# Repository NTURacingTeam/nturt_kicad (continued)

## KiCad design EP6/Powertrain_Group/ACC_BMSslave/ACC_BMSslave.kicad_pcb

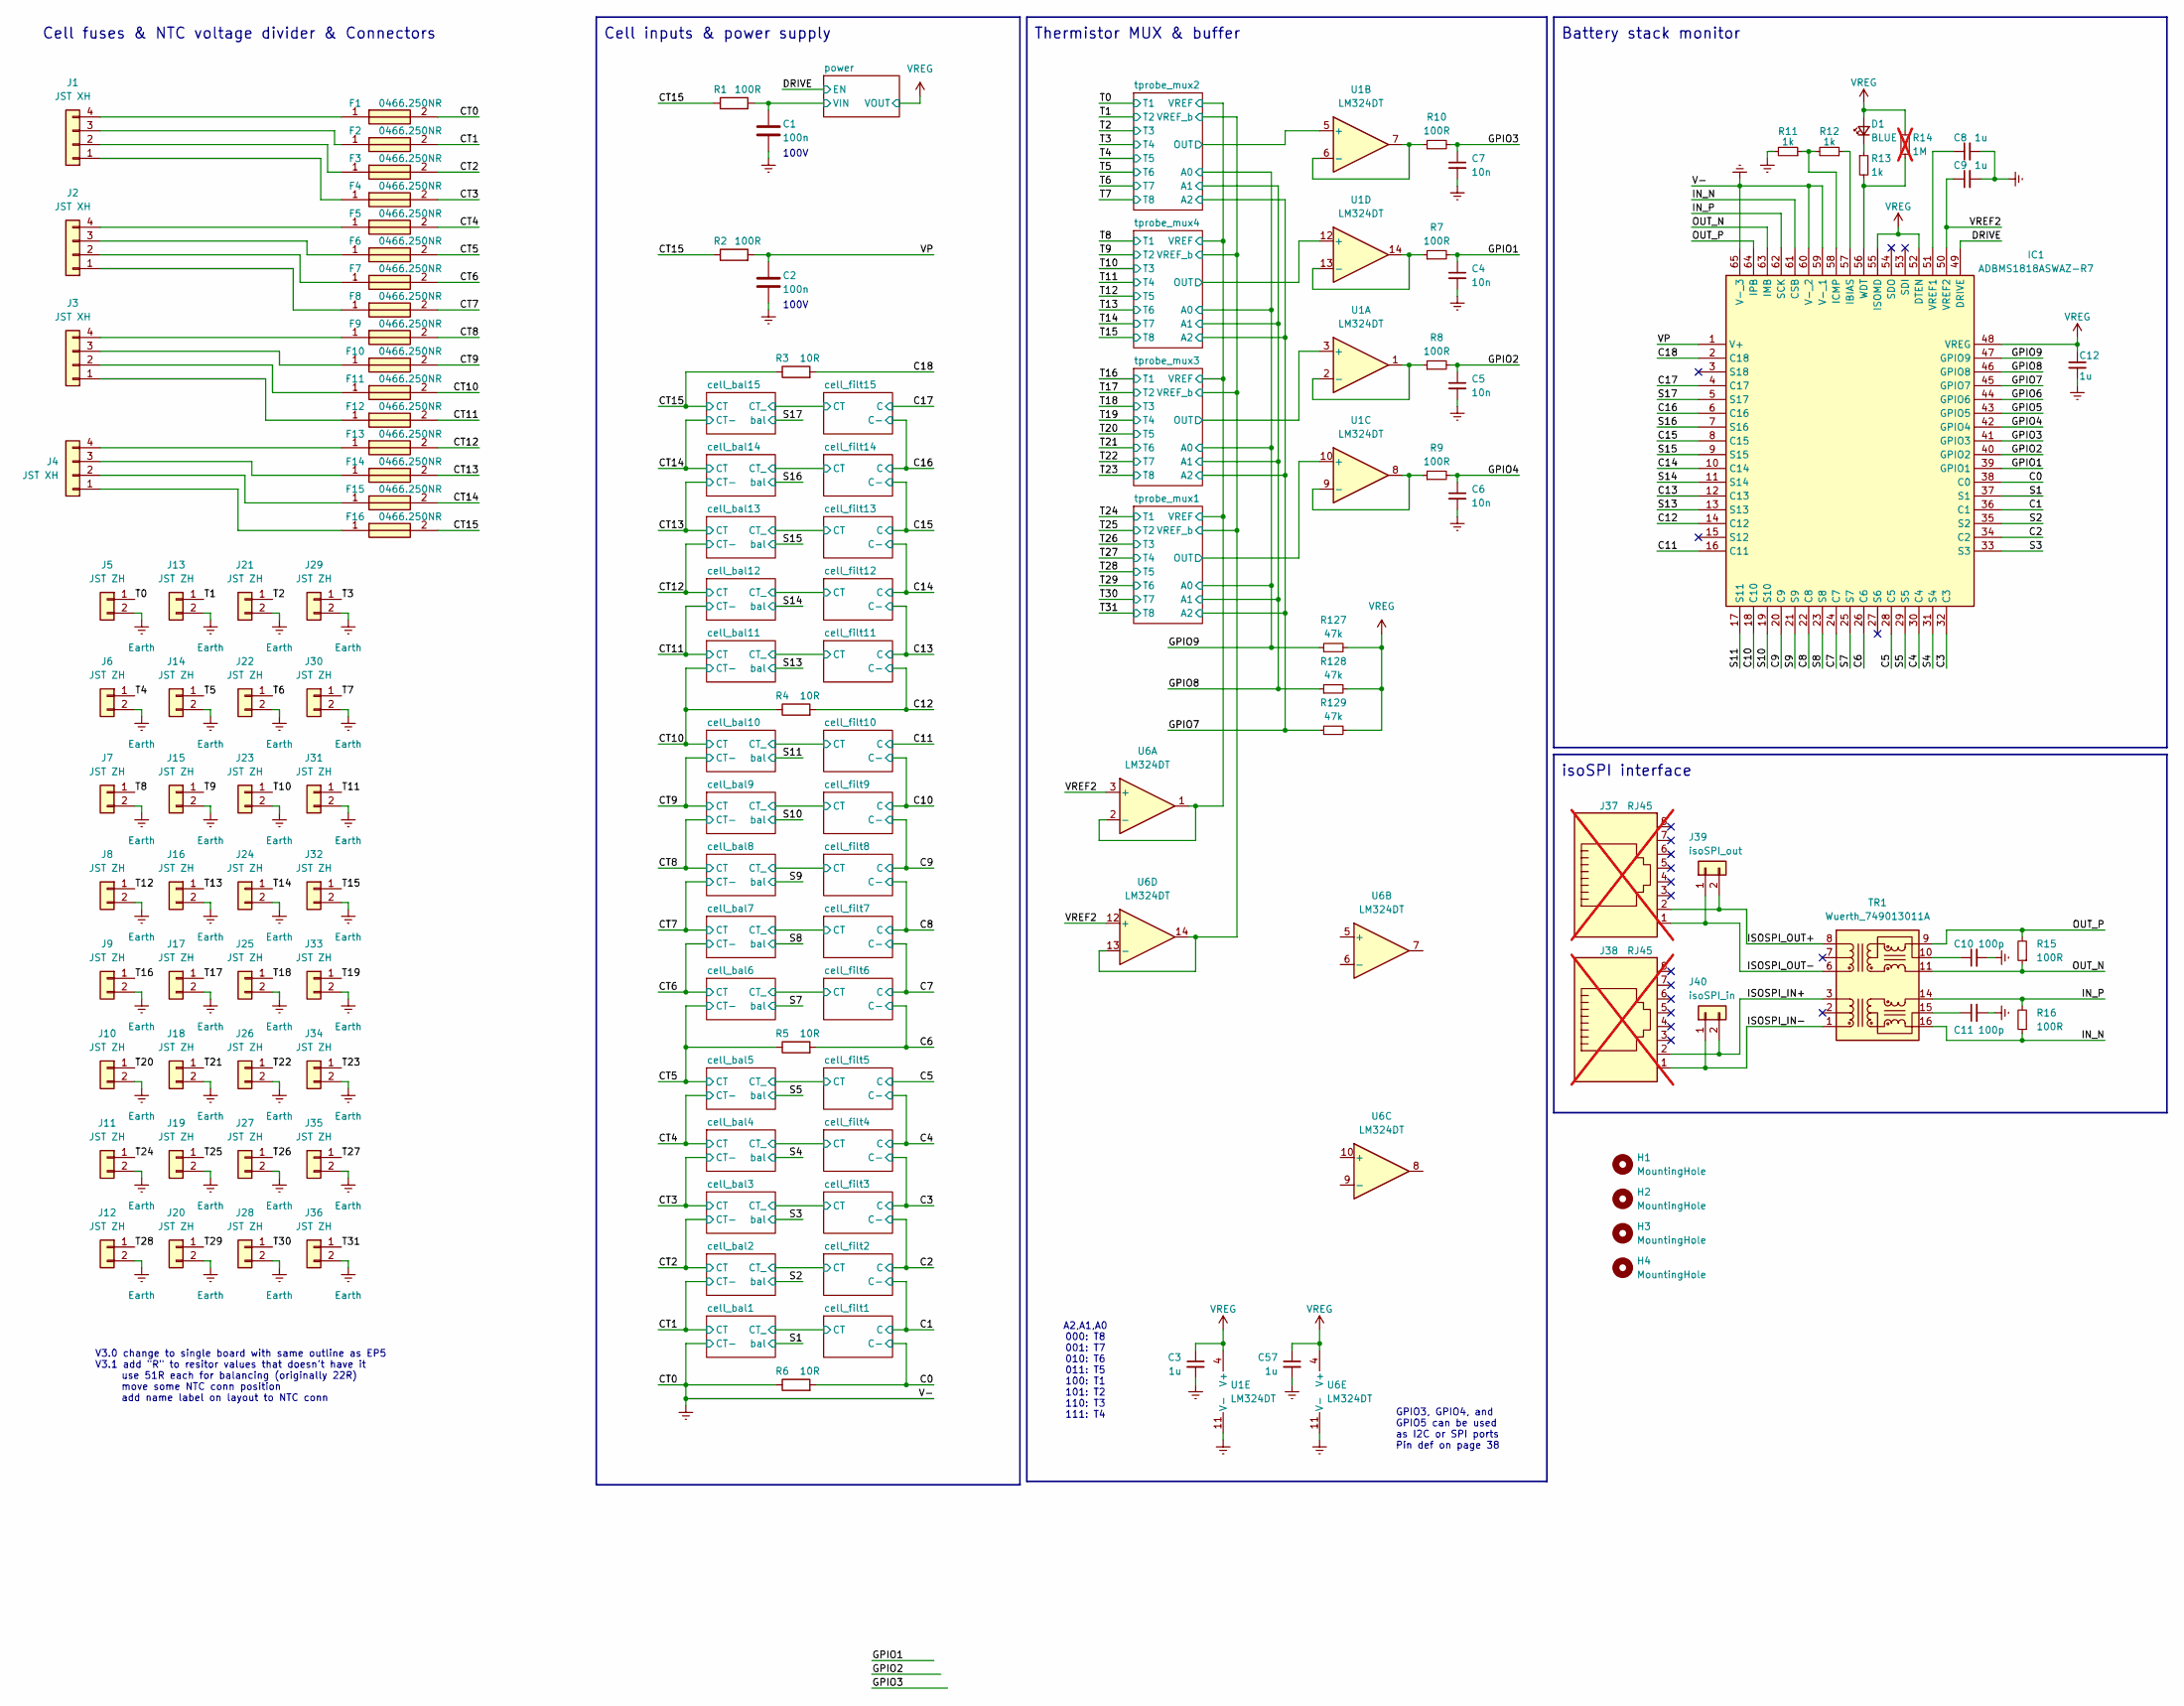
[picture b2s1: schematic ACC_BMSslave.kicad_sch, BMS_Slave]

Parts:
C1, C2: 100n; C_0603_1608Metric
C3, C57: 1u; C_0603_1608Metric
C4, C5, C6, C7: 10n; C_0402_1005Metric
C8, C9: 1u; C_0402_1005Metric
C10, C11: 100p; C_0402_1005Metric
C12: 1u; C_0805_2012Metric
D1: BLUE; LED_0603_1608Metric
F1, F2, F3, F4, F5, F6, F7, F8, F9, F10, F11, F12, F13, F14, F15, F16: 0466.250NR; Fuse_1206_3216Metric; Mouser Part Number 576-0466.250NR
H1, H2, H3, H4: MountingHole; MountingHole_4.3mm_M4_ISO14580
IC1: ADBMS1818ASWAZ-R7; LQFP-64-1EP_10x10mm_P0.5mm_EP6.5x6.5mm; Mouser Part Number 584-ADBMS1818ASWAZR7
J1, J2, J3, J4: JST XH; JST_XH_B4B-XH-A_1x04_P2.50mm_Vertical
J5, J6, J7, J8, J9, J10, J11, J12, J13, J14, J15, J16, J17, J18, J19, J20, J21, J22, J23, J24, J25, J26, J27, J28, J29, J30, J31, J32, J33, J34, J35, J36: JST ZH; JST_ZH_B2B-ZR_1x02_P1.50mm_Vertical
J37, J38: RJ45; RJ45_Amphenol_54602-x08_Horizontal; not fitted
J39: isoSPI_out; JST_XH_B2B-XH-A_1x02_P2.50mm_Vertical
J40: isoSPI_in; JST_XH_B2B-XH-A_1x02_P2.50mm_Vertical
R1: 100R; R_0805_2012Metric
R2: 100R; R_0603_1608Metric
R3, R4, R5, R6: 10R; R_0402_1005Metric
R7, R8, R9, R10, R15, R16: 100R; R_0402_1005Metric
R11, R12, R13: 1k; R_0402_1005Metric
R14: 1M; R_0603_1608Metric; not fitted
R127, R128, R129: 47k; R_0402_1005Metric
TR1: Wuerth_749013011A; Transformer_Ethernet_Wuerth_749013011A
U1, U6: LM324DT; SO-14_3.9x8.65mm_P1.27mm

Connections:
/C0: IC1.38 (C0), R6.2; also elsewhere on the board
/C1: IC1.36 (C1); also elsewhere on the board
/C2: IC1.34 (C2); also elsewhere on the board
/C3: IC1.32 (C3); also elsewhere on the board
/C4: IC1.30 (C4); also elsewhere on the board
/C5: IC1.28 (C5); also elsewhere on the board
/C6: IC1.26 (C6), R5.2; also elsewhere on the board
/C7: IC1.24 (C7); also elsewhere on the board
/C8: IC1.22 (C8); also elsewhere on the board
/C9: IC1.20 (C9); also elsewhere on the board
/C10: IC1.18 (C10); also elsewhere on the board
/C11: IC1.16 (C11); also elsewhere on the board
/C12: IC1.14 (C12), R4.2; also elsewhere on the board
/C13: IC1.12 (C13); also elsewhere on the board
/C14: IC1.10 (C14); also elsewhere on the board
/C15: IC1.8 (C15); also elsewhere on the board
/C16: IC1.6 (C16); also elsewhere on the board
/C17: IC1.4 (C17); also elsewhere on the board
/C18: IC1.2 (C18), R3.2
/CT1: F2.2; also elsewhere on the board
/CT2: F3.2; also elsewhere on the board
/CT3: F4.2; also elsewhere on the board
/CT4: F5.2; also elsewhere on the board
/CT5: F6.2, R5.1; also elsewhere on the board
/CT6: F7.2; also elsewhere on the board
/CT7: F8.2; also elsewhere on the board
/CT8: F9.2; also elsewhere on the board
/CT9: F10.2; also elsewhere on the board
/CT10: F11.2, R4.1; also elsewhere on the board
/CT11: F12.2; also elsewhere on the board
/CT12: F13.2; also elsewhere on the board
/CT13: F14.2; also elsewhere on the board
/CT14: F15.2; also elsewhere on the board
/CT15: F16.2, R1.1, R2.1, R3.1; also elsewhere on the board
/DRIVE: IC1.49 (DRIVE); also elsewhere on the board
/GPIO1: C4.1, IC1.39 (GPIO1), R7.2
/GPIO2: C5.1, IC1.40 (GPIO2), R8.2
/GPIO3: C7.1, IC1.41 (GPIO3), R10.2
/GPIO4: C6.1, IC1.42 (GPIO4), R9.2
/GPIO5: IC1.43 (GPIO5)
/GPIO6: IC1.44 (GPIO6)
/GPIO7: IC1.45 (GPIO7), R129.1; also elsewhere on the board
/GPIO8: IC1.46 (GPIO8), R128.1; also elsewhere on the board
/GPIO9: IC1.47 (GPIO9), R127.1; also elsewhere on the board
/IN_N: IC1.61 (CSB), R16.1, TR1.16 (TX+)
/IN_P: IC1.62 (SCK), R16.2, TR1.14 (TX-)
/ISOSPI_IN+: J38.2, J40.2, TR1.3 (TD-)
/ISOSPI_IN-: J38.1, J40.1, TR1.1 (TD+)
/ISOSPI_OUT+: J37.2, J39.2, TR1.8 (RD-)
/ISOSPI_OUT-: J37.1, J39.1, TR1.6 (RD+)
/OUT_N: IC1.63 (IMB), R15.1, TR1.11 (RX+)
/OUT_P: IC1.64 (IPB), R15.2, TR1.9 (RX-)
/S1: IC1.37 (S1); also elsewhere on the board
/S2: IC1.35 (S2); also elsewhere on the board
/S3: IC1.33 (S3); also elsewhere on the board
/S4: IC1.31 (S4); also elsewhere on the board
/S5: IC1.29 (S5); also elsewhere on the board
/S7: IC1.25 (S7); also elsewhere on the board
/S8: IC1.23 (S8); also elsewhere on the board
/S9: IC1.21 (S9); also elsewhere on the board
/S10: IC1.19 (S10); also elsewhere on the board
/S11: IC1.17 (S11); also elsewhere on the board
/S13: IC1.13 (S13); also elsewhere on the board
/S14: IC1.11 (S14); also elsewhere on the board
/S15: IC1.9 (S15); also elsewhere on the board
/S16: IC1.7 (S16); also elsewhere on the board
/S17: IC1.5 (S17); also elsewhere on the board
/T0: J5.1; also elsewhere on the board
/T1: J13.1; also elsewhere on the board
/T2: J21.1; also elsewhere on the board
/T3: J29.1; also elsewhere on the board
/T4: J6.1; also elsewhere on the board
/T5: J14.1; also elsewhere on the board
/T6: J22.1; also elsewhere on the board
/T7: J30.1; also elsewhere on the board
/T8: J7.1; also elsewhere on the board
/T9: J15.1; also elsewhere on the board
/T10: J23.1; also elsewhere on the board
/T11: J31.1; also elsewhere on the board
/T12: J8.1; also elsewhere on the board
/T13: J16.1; also elsewhere on the board
/T14: J24.1; also elsewhere on the board
/T15: J32.1; also elsewhere on the board
/T16: J9.1; also elsewhere on the board
/T17: J17.1; also elsewhere on the board
/T18: J25.1; also elsewhere on the board
/T19: J33.1; also elsewhere on the board
/T20: J10.1; also elsewhere on the board
/T21: J18.1; also elsewhere on the board
/T22: J26.1; also elsewhere on the board
/T23: J34.1; also elsewhere on the board
/T24: J11.1; also elsewhere on the board
/T25: J19.1; also elsewhere on the board
/T26: J27.1; also elsewhere on the board
/T27: J35.1; also elsewhere on the board
/T28: J12.1; also elsewhere on the board
/T29: J20.1; also elsewhere on the board
/T30: J28.1; also elsewhere on the board
/T31: J36.1; also elsewhere on the board
/VP: C2.1, IC1.1 (V+), R2.2
/VREF2: C9.1, IC1.50 (VREF2), U6.3 (+), U6.12 (+)
/power/VIN: C1.1, R1.2; also elsewhere on the board
/tprobe_mux1/OUT: U1.10 (+); also elsewhere on the board
/tprobe_mux2/OUT: U1.5 (+); also elsewhere on the board
/tprobe_mux3/OUT: U1.3 (+); also elsewhere on the board
/tprobe_mux4/OUT: U1.12 (+); also elsewhere on the board
Earth: C1.2, C2.2, C3.2, C4.2, C5.2, C6.2, C7.2, C8.2, C9.2, C10.2, C11.2, C12.2, C57.2, F1.2, IC1.59 (V-_1), IC1.60 (V-_2), IC1.65 (V-_3), J5.2, J6.2, J7.2, J8.2, J9.2, J10.2, J11.2, J12.2, J13.2, J14.2, J15.2, J16.2, J17.2, J18.2, J19.2, J20.2, J21.2, J22.2, J23.2, J24.2, J25.2, J26.2, J27.2, J28.2, J29.2, J30.2, J31.2, J32.2, J33.2, J34.2, J35.2, J36.2, R6.1, R11.2, U1.11 (V-), U6.11 (V-); also elsewhere on the board
unnamed: D1.1 (K), R13.1
unnamed: IC1.57 (IBIAS), R12.1
unnamed: IC1.58 (ICMP), R11.1, R12.2
unnamed: C8.1, IC1.51 (VREF1)
unnamed: IC1.56 (WDT), R13.2, R14.2
unnamed: F4.1, J1.1
unnamed: F3.1, J1.2
unnamed: F2.1, J1.3
unnamed: F1.1, J1.4
unnamed: F8.1, J2.1
unnamed: F7.1, J2.2
unnamed: F6.1, J2.3
unnamed: F5.1, J2.4
unnamed: F12.1, J3.1
unnamed: F11.1, J3.2
unnamed: F10.1, J3.3
unnamed: F9.1, J3.4
unnamed: F16.1, J4.1
unnamed: F15.1, J4.2
unnamed: F14.1, J4.3
unnamed: F13.1, J4.4
unnamed: C10.1, TR1.10 (C_RX)
unnamed: C11.1, TR1.15 (C_TX)
unnamed: R8.1, U1.1, U1.2 (-)
unnamed: R10.1, U1.6 (-), U1.7
unnamed: R9.1, U1.8, U1.9 (-)
unnamed: R7.1, U1.13 (-), U1.14
VREG: C3.1, C12.1, C57.1, D1.2 (A), IC1.48 (VREG), IC1.52 (DTEN), IC1.55 (ISOMD), R14.1, R127.2, R128.2, R129.2, U1.4 (V+), U6.4 (V+); also elsewhere on the board

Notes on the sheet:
Cell inputs & power supply
A2,A1,A0 000: T8 001: T7 010: T6 011: T5 100: T1 101: T2 110: T3 111: T4
V3.0 change to single board with same outline as EP5 V3.1 add "R" to resitor values that doesn't have it use 51R each for balancing (originally 22R) move some NTC conn position add name label on layout to NTC conn
GPIO3, GPIO4, and GPIO5 can be used as I2C or SPI ports Pin def on page 38
isoSPI interface
Battery stack monitor
100V
Thermistor MUX & buffer
Cell fuses & NTC voltage divider & Connectors

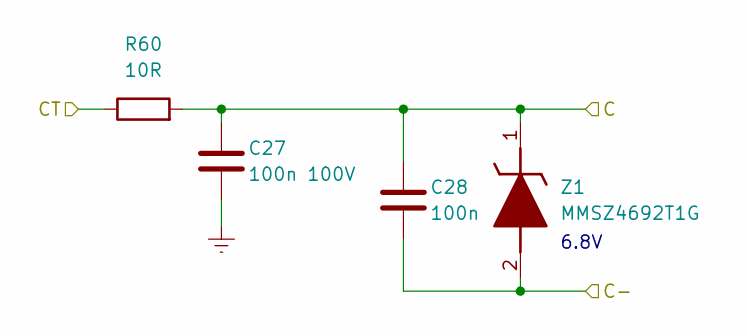
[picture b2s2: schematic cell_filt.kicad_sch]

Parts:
C27: 100n 100V; C_0805_2012Metric
C28: 100n; C_0402_1005Metric
R60: 10R; R_0402_1005Metric
Z1: MMSZ4692T1G; D_SOD-123; Mouser Part Number 863-MMSZ4692T1G

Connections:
/C1: C28.2, Z1.2 (A); also elsewhere on the board
/C2: C27.1, C28.1, R60.2, Z1.1 (K); also elsewhere on the board
/CT2: R60.1; also elsewhere on the board
Earth: C27.2; also elsewhere on the board

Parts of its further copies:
C29, C31, C33, C35, C37, C39, C41, C43, C45, C47, C49, C51, C53, C55: 100n 100V; C_0805_2012Metric
C30, C32, C34, C36, C38, C40, C42, C44, C46, C48, C50, C52, C54, C56: 100n; C_0402_1005Metric
R65, R70, R75, R80, R85, R90, R95, R96, R101, R122, R123, R124, R125, R126: 10R; R_0402_1005Metric
Z2, Z3, Z4, Z5, Z6, Z7, Z8, Z9, Z10, Z11, Z12, Z13, Z14, Z15: MMSZ4692T1G; D_SOD-123; Mouser Part Number 863-MMSZ4692T1G

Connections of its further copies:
/C0: C42.2, Z8.2 (A); also elsewhere on the board
/C1: C41.1, C42.1, R95.2, Z8.1 (K); also elsewhere on the board
/C2: C30.2, Z2.2 (A); also elsewhere on the board
/C3: C29.1, C30.1, C32.2, R65.2, Z2.1 (K), Z3.2 (A); also elsewhere on the board
/C4: C31.1, C32.1, C34.2, R70.2, Z3.1 (K), Z4.2 (A); also elsewhere on the board
/C5: C33.1, C34.1, R75.2, Z4.1 (K); also elsewhere on the board
/C6: C36.2, Z5.2 (A); also elsewhere on the board
/C7: C35.1, C36.1, C38.2, R80.2, Z5.1 (K), Z6.2 (A); also elsewhere on the board
/C8: C37.1, C38.1, C40.2, R85.2, Z6.1 (K), Z7.2 (A); also elsewhere on the board
/C9: C39.1, C40.1, C44.2, R90.2, Z7.1 (K), Z9.2 (A); also elsewhere on the board
/C10: C43.1, C44.1, C46.2, R96.2, Z9.1 (K), Z10.2 (A); also elsewhere on the board
/C11: C45.1, C46.1, R101.2, Z10.1 (K); also elsewhere on the board
/C12: C48.2, Z11.2 (A); also elsewhere on the board
/C13: C47.1, C48.1, C50.2, R122.2, Z11.1 (K), Z12.2 (A); also elsewhere on the board
/C14: C49.1, C50.1, C52.2, R123.2, Z12.1 (K), Z13.2 (A); also elsewhere on the board
/C15: C51.1, C52.1, C54.2, R124.2, Z13.1 (K), Z14.2 (A); also elsewhere on the board
/C16: C53.1, C54.1, C56.2, R125.2, Z14.1 (K), Z15.2 (A); also elsewhere on the board
/C17: C55.1, C56.1, R126.2, Z15.1 (K); also elsewhere on the board
/CT1: R95.1; also elsewhere on the board
/CT3: R65.1; also elsewhere on the board
/CT4: R70.1; also elsewhere on the board
/CT5: R75.1; also elsewhere on the board
/CT6: R80.1; also elsewhere on the board
/CT7: R85.1; also elsewhere on the board
/CT8: R90.1; also elsewhere on the board
/CT9: R96.1; also elsewhere on the board
/CT10: R101.1; also elsewhere on the board
/CT11: R122.1; also elsewhere on the board
/CT12: R123.1; also elsewhere on the board
/CT13: R124.1; also elsewhere on the board
/CT14: R125.1; also elsewhere on the board
/CT15: R126.1; also elsewhere on the board
Earth: C29.2, C31.2, C33.2, C35.2, C37.2, C39.2, C41.2, C43.2, C45.2, C47.2, C49.2, C51.2, C53.2, C55.2; also elsewhere on the board

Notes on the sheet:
6.8V

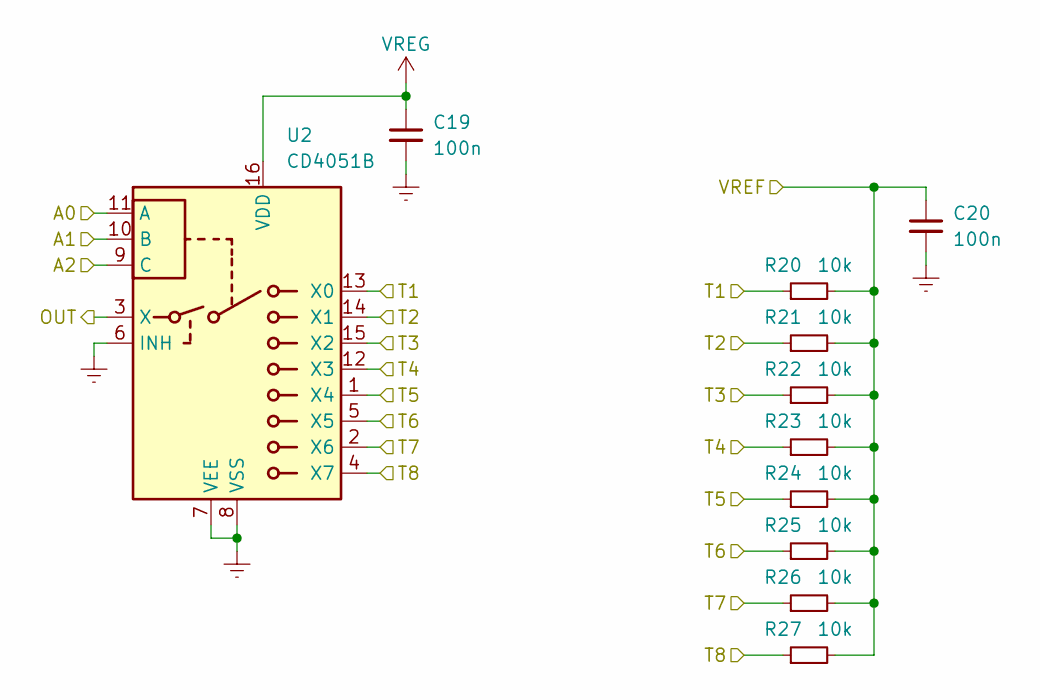
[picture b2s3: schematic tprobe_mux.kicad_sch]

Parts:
C19, C20: 100n; C_0402_1005Metric
R20, R21, R22, R23, R24, R25, R26, R27: 10k; R_0402_1005Metric
U2: CD4051B; TSSOP-16_4.4x5mm_P0.65mm

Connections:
/GPIO7: U2.9 (C); also elsewhere on the board
/GPIO8: U2.10 (B); also elsewhere on the board
/GPIO9: U2.11 (A); also elsewhere on the board
/T24: R20.1, U2.13 (X0); also elsewhere on the board
/T25: R21.1, U2.14 (X1); also elsewhere on the board
/T26: R22.1, U2.15 (X2); also elsewhere on the board
/T27: R23.1, U2.12 (X3); also elsewhere on the board
/T28: R24.1, U2.1 (X4); also elsewhere on the board
/T29: R25.1, U2.5 (X5); also elsewhere on the board
/T30: R26.1, U2.2 (X6); also elsewhere on the board
/T31: R27.1, U2.4 (X7); also elsewhere on the board
/tprobe_mux1/OUT: U2.3 (X); also elsewhere on the board
Earth: C19.2, C20.2, U2.6 (INH), U2.7 (VEE), U2.8 (VSS); also elsewhere on the board
VREG: C19.1, U2.16 (VDD); also elsewhere on the board

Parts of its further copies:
C21, C22, C23, C24, C25, C26: 100n; C_0402_1005Metric
R28, R29, R30, R31, R32, R33, R34, R35, R36, R37, R38, R39, R40, R41, R42, R43, R44, R45, R46, R47, R48, R49, R50, R51: 10k; R_0402_1005Metric
U3, U4, U5: CD4051B; TSSOP-16_4.4x5mm_P0.65mm

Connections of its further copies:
/GPIO7: U3.9 (C), U4.9 (C), U5.9 (C); also elsewhere on the board
/GPIO8: U3.10 (B), U4.10 (B), U5.10 (B); also elsewhere on the board
/GPIO9: U3.11 (A), U4.11 (A), U5.11 (A); also elsewhere on the board
/T0: R28.1, U3.13 (X0); also elsewhere on the board
/T1: R29.1, U3.14 (X1); also elsewhere on the board
/T2: R30.1, U3.15 (X2); also elsewhere on the board
/T3: R31.1, U3.12 (X3); also elsewhere on the board
/T4: R32.1, U3.1 (X4); also elsewhere on the board
/T5: R33.1, U3.5 (X5); also elsewhere on the board
/T6: R34.1, U3.2 (X6); also elsewhere on the board
/T7: R35.1, U3.4 (X7); also elsewhere on the board
/T8: R44.1, U5.13 (X0); also elsewhere on the board
/T9: R45.1, U5.14 (X1); also elsewhere on the board
/T10: R46.1, U5.15 (X2); also elsewhere on the board
/T11: R47.1, U5.12 (X3); also elsewhere on the board
/T12: R48.1, U5.1 (X4); also elsewhere on the board
/T13: R49.1, U5.5 (X5); also elsewhere on the board
/T14: R50.1, U5.2 (X6); also elsewhere on the board
/T15: R51.1, U5.4 (X7); also elsewhere on the board
/T16: R36.1, U4.13 (X0); also elsewhere on the board
/T17: R37.1, U4.14 (X1); also elsewhere on the board
/T18: R38.1, U4.15 (X2); also elsewhere on the board
/T19: R39.1, U4.12 (X3); also elsewhere on the board
/T20: R40.1, U4.1 (X4); also elsewhere on the board
/T21: R41.1, U4.5 (X5); also elsewhere on the board
/T22: R42.1, U4.2 (X6); also elsewhere on the board
/T23: R43.1, U4.4 (X7); also elsewhere on the board
/tprobe_mux2/OUT: U3.3 (X); also elsewhere on the board
/tprobe_mux3/OUT: U4.3 (X); also elsewhere on the board
/tprobe_mux4/OUT: U5.3 (X); also elsewhere on the board
Earth: C21.2, C22.2, C23.2, C24.2, C25.2, C26.2, U3.6 (INH), U3.7 (VEE), U3.8 (VSS), U4.6 (INH), U4.7 (VEE), U4.8 (VSS), U5.6 (INH), U5.7 (VEE), U5.8 (VSS); also elsewhere on the board
VREG: C21.1, C23.1, C25.1, U3.16 (VDD), U4.16 (VDD), U5.16 (VDD); also elsewhere on the board

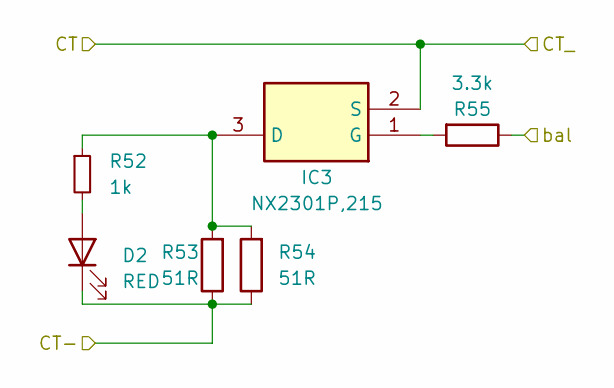
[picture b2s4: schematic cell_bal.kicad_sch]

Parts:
D2: RED; LED_0603_1608Metric
IC3: NX2301P,215; SOT-23; Mouser Part Number 771-NX2301P215
R52: 1k; R_0402_1005Metric
R53, R54: 51R; R_2512_6332Metric
R55: 3.3k; R_0402_1005Metric

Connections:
/CT1: D2.1 (K), R53.1, R54.1; also elsewhere on the board
/CT2: IC3.2 (S); also elsewhere on the board
/S2: R55.1; also elsewhere on the board
unnamed: D2.2 (A), R52.2
unnamed: IC3.3 (D), R52.1, R53.2, R54.2
unnamed: IC3.1 (G), R55.2

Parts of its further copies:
D3, D4, D5, D6, D7, D8, D9, D10, D11, D12, D13, D14, D15, D16: RED; LED_0603_1608Metric
IC4, IC5, IC6, IC7, IC8, IC9, IC10, IC11, IC12, IC13, IC14, IC15, IC16, IC17: NX2301P,215; SOT-23; Mouser Part Number 771-NX2301P215
R56, R61, R66, R71, R76, R81, R86, R91, R97, R102, R106, R110, R114, R118: 1k; R_0402_1005Metric
R57, R58, R62, R63, R67, R68, R72, R73, R77, R78, R82, R83, R87, R88, R92, R93, R98, R99, R103, R104, R107, R108, R111, R112, R115, R116, R119, R120: 51R; R_2512_6332Metric
R59, R64, R69, R74, R79, R84, R89, R94, R100, R105, R109, R113, R117, R121: 3.3k; R_0402_1005Metric

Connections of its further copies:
/CT1: IC4.2 (S); also elsewhere on the board
/CT2: D4.1 (K), R62.1, R63.1; also elsewhere on the board
/CT3: D5.1 (K), IC5.2 (S), R67.1, R68.1; also elsewhere on the board
/CT4: D6.1 (K), IC6.2 (S), R72.1, R73.1; also elsewhere on the board
/CT5: D7.1 (K), IC7.2 (S), R77.1, R78.1; also elsewhere on the board
/CT6: D8.1 (K), IC8.2 (S), R82.1, R83.1; also elsewhere on the board
/CT7: D9.1 (K), IC9.2 (S), R87.1, R88.1; also elsewhere on the board
/CT8: D10.1 (K), IC10.2 (S), R92.1, R93.1; also elsewhere on the board
/CT9: D11.1 (K), IC11.2 (S), R98.1, R99.1; also elsewhere on the board
/CT10: D12.1 (K), IC12.2 (S), R103.1, R104.1; also elsewhere on the board
/CT11: D13.1 (K), IC13.2 (S), R107.1, R108.1; also elsewhere on the board
/CT12: D14.1 (K), IC14.2 (S), R111.1, R112.1; also elsewhere on the board
/CT13: D15.1 (K), IC15.2 (S), R115.1, R116.1; also elsewhere on the board
/CT14: D16.1 (K), IC16.2 (S), R119.1, R120.1; also elsewhere on the board
/CT15: IC17.2 (S); also elsewhere on the board
/S1: R59.1; also elsewhere on the board
/S3: R64.1; also elsewhere on the board
/S4: R69.1; also elsewhere on the board
/S5: R74.1; also elsewhere on the board
/S7: R79.1; also elsewhere on the board
/S8: R84.1; also elsewhere on the board
/S9: R89.1; also elsewhere on the board
/S10: R94.1; also elsewhere on the board
/S11: R100.1; also elsewhere on the board
/S13: R105.1; also elsewhere on the board
/S14: R109.1; also elsewhere on the board
/S15: R113.1; also elsewhere on the board
/S16: R117.1; also elsewhere on the board
/S17: R121.1; also elsewhere on the board
Earth: D3.1 (K), R57.1, R58.1; also elsewhere on the board
unnamed: D3.2 (A), R56.2
unnamed: D4.2 (A), R61.2
unnamed: D5.2 (A), R66.2
unnamed: D6.2 (A), R71.2
unnamed: D7.2 (A), R76.2
unnamed: D8.2 (A), R81.2
unnamed: D9.2 (A), R86.2
unnamed: D10.2 (A), R91.2
unnamed: D11.2 (A), R97.2
unnamed: D12.2 (A), R102.2
unnamed: D13.2 (A), R106.2
unnamed: D14.2 (A), R110.2
unnamed: D15.2 (A), R114.2
unnamed: D16.2 (A), R118.2
unnamed: IC4.3 (D), R56.1, R57.2, R58.2
unnamed: IC4.1 (G), R59.2
unnamed: IC5.3 (D), R61.1, R62.2, R63.2
unnamed: IC5.1 (G), R64.2
unnamed: IC6.3 (D), R66.1, R67.2, R68.2
unnamed: IC6.1 (G), R69.2
unnamed: IC7.3 (D), R71.1, R72.2, R73.2
unnamed: IC7.1 (G), R74.2
unnamed: IC8.3 (D), R76.1, R77.2, R78.2
unnamed: IC8.1 (G), R79.2
unnamed: IC9.3 (D), R81.1, R82.2, R83.2
unnamed: IC9.1 (G), R84.2
unnamed: IC10.3 (D), R86.1, R87.2, R88.2
unnamed: IC10.1 (G), R89.2
unnamed: IC11.3 (D), R91.1, R92.2, R93.2
unnamed: IC11.1 (G), R94.2
unnamed: IC12.3 (D), R97.1, R98.2, R99.2
unnamed: IC12.1 (G), R100.2
unnamed: IC13.3 (D), R102.1, R103.2, R104.2
unnamed: IC13.1 (G), R105.2
unnamed: IC14.3 (D), R106.1, R107.2, R108.2
unnamed: IC14.1 (G), R109.2
unnamed: IC15.3 (D), R110.1, R111.2, R112.2
unnamed: IC15.1 (G), R113.2
unnamed: IC16.3 (D), R114.1, R115.2, R116.2
unnamed: IC16.1 (G), R117.2
unnamed: IC17.3 (D), R118.1, R119.2, R120.2
unnamed: IC17.1 (G), R121.2

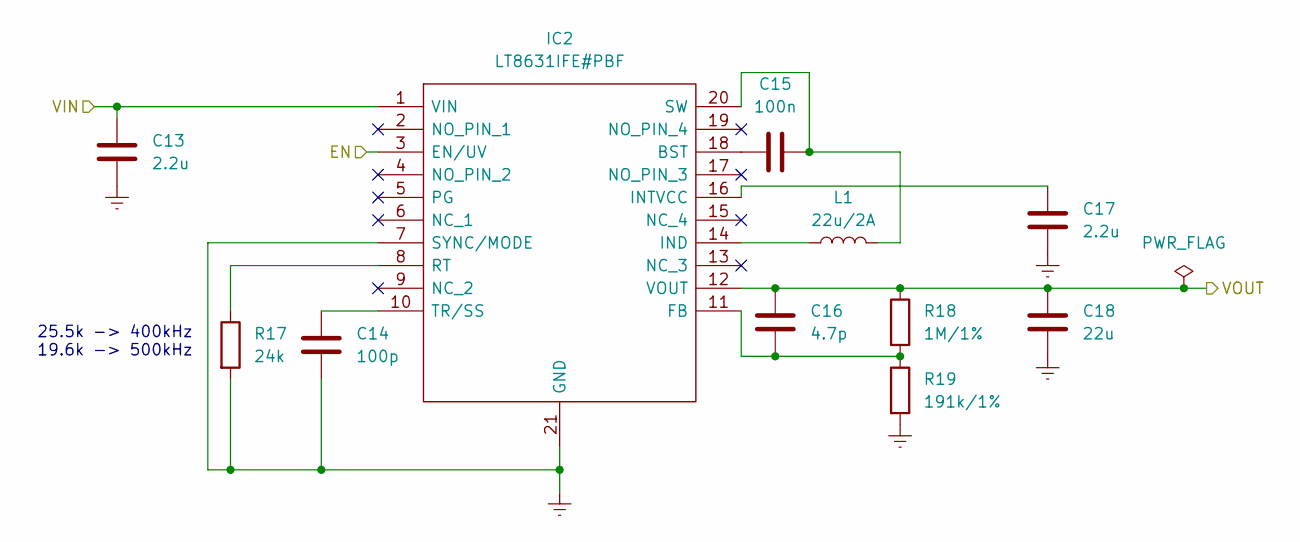
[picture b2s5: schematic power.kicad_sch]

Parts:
C13: 2.2u; C_2220_5750Metric
C14: 100p; C_0603_1608Metric
C15: 100n; C_0603_1608Metric
C16: 4.7p; C_0402_1005Metric
C17: 2.2u; C_0603_1608Metric
C18: 22u; C_1206_3216Metric
IC2: LT8631IFE#PBF; TSSOP-20 FE20(16) (EP Variation CB); Mouser Part Number 584-LT8631IFE#PBF
L1: 22u/2A; L_Bourns-SRN8040_8x8.15mm
R17: 24k; R_0402_1005Metric
R18: 1M/1%; R_0402_1005Metric
R19: 191k/1%; R_0402_1005Metric

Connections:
/DRIVE: IC2.3 (EN/UV); also elsewhere on the board
/power/VIN: C13.1, IC2.1 (VIN); also elsewhere on the board
Earth: C13.2, C14.2, C17.2, C18.2, IC2.7 (SYNC/MODE), IC2.21 (GND), R17.2, R19.2; also elsewhere on the board
unnamed: C15.1, IC2.18 (BST)
unnamed: C16.1, IC2.11 (FB), R18.2, R19.1
unnamed: IC2.14 (IND), L1.1
unnamed: C17.1, IC2.16 (INTVCC)
unnamed: IC2.8 (RT), R17.1
unnamed: C15.2, IC2.20 (SW), L1.2
unnamed: C14.1, IC2.10 (TR/SS)
VREG: C16.2, C18.1, IC2.12 (VOUT), R18.1; also elsewhere on the board

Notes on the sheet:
25.5k -> 400kHz 19.6k -> 500kHz

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
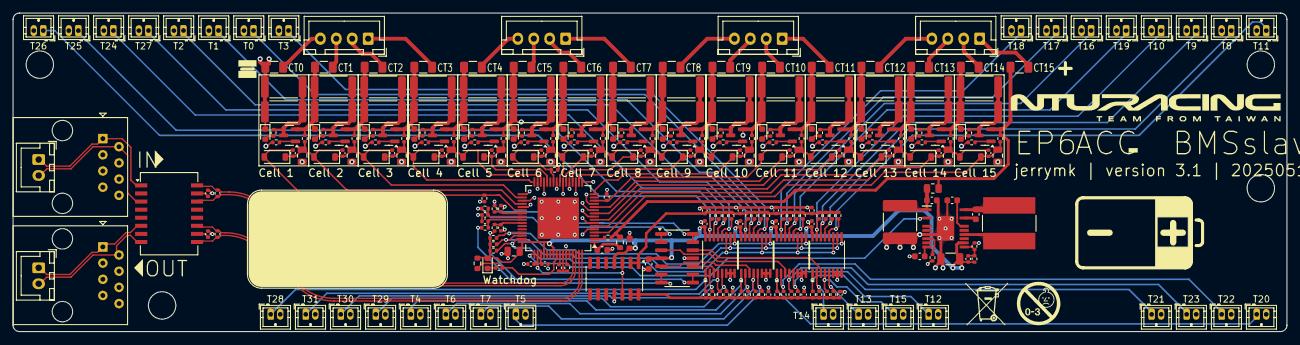
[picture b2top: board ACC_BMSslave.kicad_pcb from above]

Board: 4 copper layers, 200.0 x 50.0 mm, 306 parts (0 on the bottom side), 187 nets.

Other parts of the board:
C58, C59, C60, C61: 100n; C_0402_1005Metric

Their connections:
Earth: C58.2, C59.2, C60.2, C61.2; also elsewhere on the board

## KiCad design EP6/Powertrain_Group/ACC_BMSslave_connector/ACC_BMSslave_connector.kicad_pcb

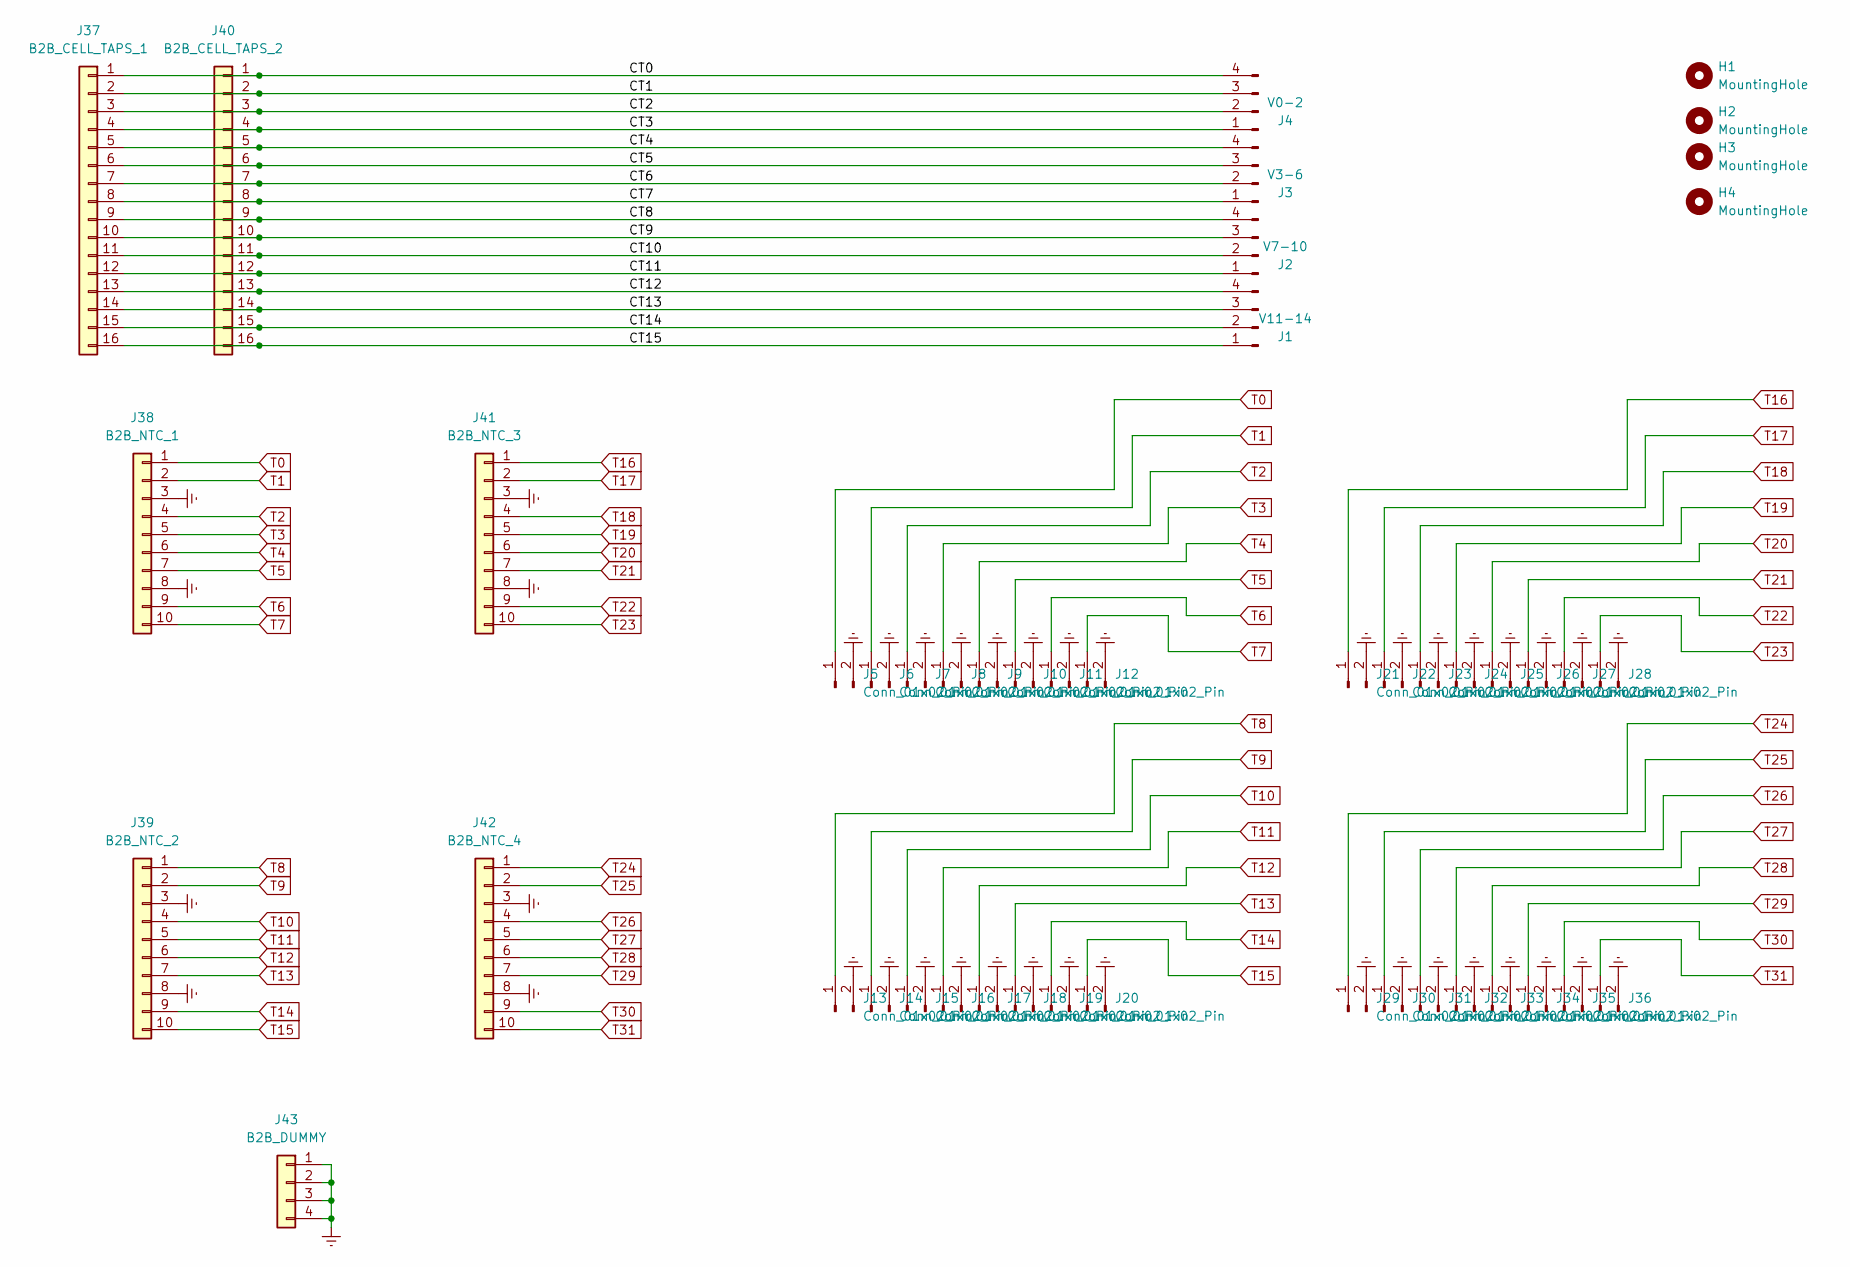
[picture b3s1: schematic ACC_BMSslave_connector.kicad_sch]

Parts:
H1, H2, H3, H4: MountingHole; MountingHole_4.3mm_M4_DIN965
J1: V11-14; JST_XH_S4B-XH-A_1x04_P2.50mm_Horizontal
J2: V7-10; JST_XH_S4B-XH-A_1x04_P2.50mm_Horizontal
J3: V3-6; JST_XH_S4B-XH-A_1x04_P2.50mm_Horizontal
J4: V0-2; JST_XH_S4B-XH-A_1x04_P2.50mm_Horizontal
J5, J6, J7, J8, J9, J10, J11, J12, J13, J14, J15, J16, J17, J18, J19, J20, J21, J22, J23, J24, J25, J26, J27, J28, J29, J30, J31, J32, J33, J34, J35, J36: Conn_01x02_Pin; SHDR2W50P0X150_1X2_450X350X450P
J37: B2B_CELL_TAPS_1; PinSocket_1x16_P2.54mm_Vertical
J38: B2B_NTC_1; PinSocket_1x10_P2.54mm_Vertical
J39: B2B_NTC_2; PinSocket_1x10_P2.54mm_Vertical
J40: B2B_CELL_TAPS_2; PinSocket_1x16_P2.54mm_Vertical
J41: B2B_NTC_3; PinSocket_1x10_P2.54mm_Vertical
J42: B2B_NTC_4; PinSocket_1x10_P2.54mm_Vertical
J43: B2B_DUMMY; PinSocket_1x04_P2.54mm_Vertical

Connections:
/CT0: J4.4, J37.1, J40.1
/CT1: J4.3, J37.2, J40.2
/CT2: J4.2, J37.3, J40.3
/CT3: J4.1, J37.4, J40.4
/CT4: J3.4, J37.5, J40.5
/CT5: J3.3, J37.6, J40.6
/CT6: J3.2, J37.7, J40.7
/CT7: J3.1, J37.8, J40.8
/CT8: J2.4, J37.9, J40.9
/CT9: J2.3, J37.10, J40.10
/CT10: J2.2, J37.11, J40.11
/CT11: J2.1, J37.12, J40.12
/CT12: J1.4, J37.13, J40.13
/CT13: J1.3, J37.14, J40.14
/CT14: J1.2, J37.15, J40.15
/CT15: J1.1, J37.16, J40.16
Earth: J5.2, J6.2, J7.2, J8.2, J9.2, J10.2, J11.2, J12.2, J13.2, J14.2, J15.2, J16.2, J17.2, J18.2, J19.2, J20.2, J21.2, J22.2, J23.2, J24.2, J25.2, J26.2, J27.2, J28.2, J29.2, J30.2, J31.2, J32.2, J33.2, J34.2, J35.2, J36.2, J38.3, J38.8, J39.3, J39.8, J41.3, J41.8, J42.3, J42.8, J43.1, J43.2, J43.3, J43.4
T0: J5.1, J38.1
T1: J6.1, J38.2
T2: J7.1, J38.4
T3: J8.1, J38.5
T4: J9.1, J38.6
T5: J10.1, J38.7
T6: J11.1, J38.9
T7: J12.1, J38.10
T8: J13.1, J39.1
T9: J14.1, J39.2
T10: J15.1, J39.4
T11: J16.1, J39.5
T12: J17.1, J39.6
T13: J18.1, J39.7
T14: J19.1, J39.9
T15: J20.1, J39.10
T16: J21.1, J41.1
T17: J22.1, J41.2
T18: J23.1, J41.4
T19: J24.1, J41.5
T20: J25.1, J41.6
T21: J26.1, J41.7
T22: J27.1, J41.9
T23: J28.1, J41.10
T24: J29.1, J42.1
T25: J30.1, J42.2
T26: J31.1, J42.4
T27: J32.1, J42.5
T28: J33.1, J42.6
T29: J34.1, J42.7
T30: J35.1, J42.9
T31: J36.1, J42.10

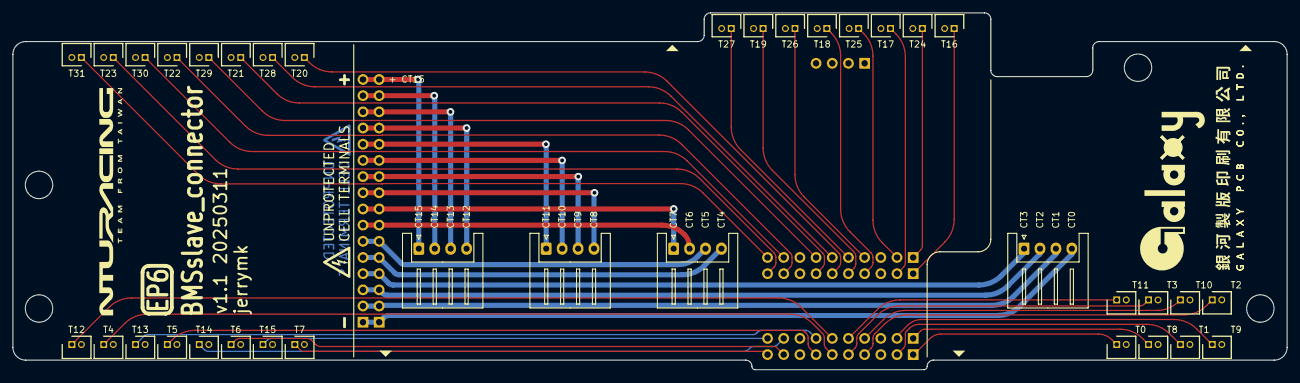
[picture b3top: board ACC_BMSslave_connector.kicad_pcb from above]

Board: 4 copper layers, 200.0 x 56.0 mm, 47 parts (0 on the bottom side), 49 nets.
